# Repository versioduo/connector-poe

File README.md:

# ⚡ V2 Link + Power Over Ethernet Mode B 

## Board

## Schematic

[PDF](connector-poe.pdf)

## Bill Of Materials

[Interactive BOM](https://htmlpreview.github.io/?https://github.com/versioduo/connector-poe/main/connector-poe-bom.html)

# Copying
Anyone can use this public domain work without having to seek authorisation, no one can ever own it.

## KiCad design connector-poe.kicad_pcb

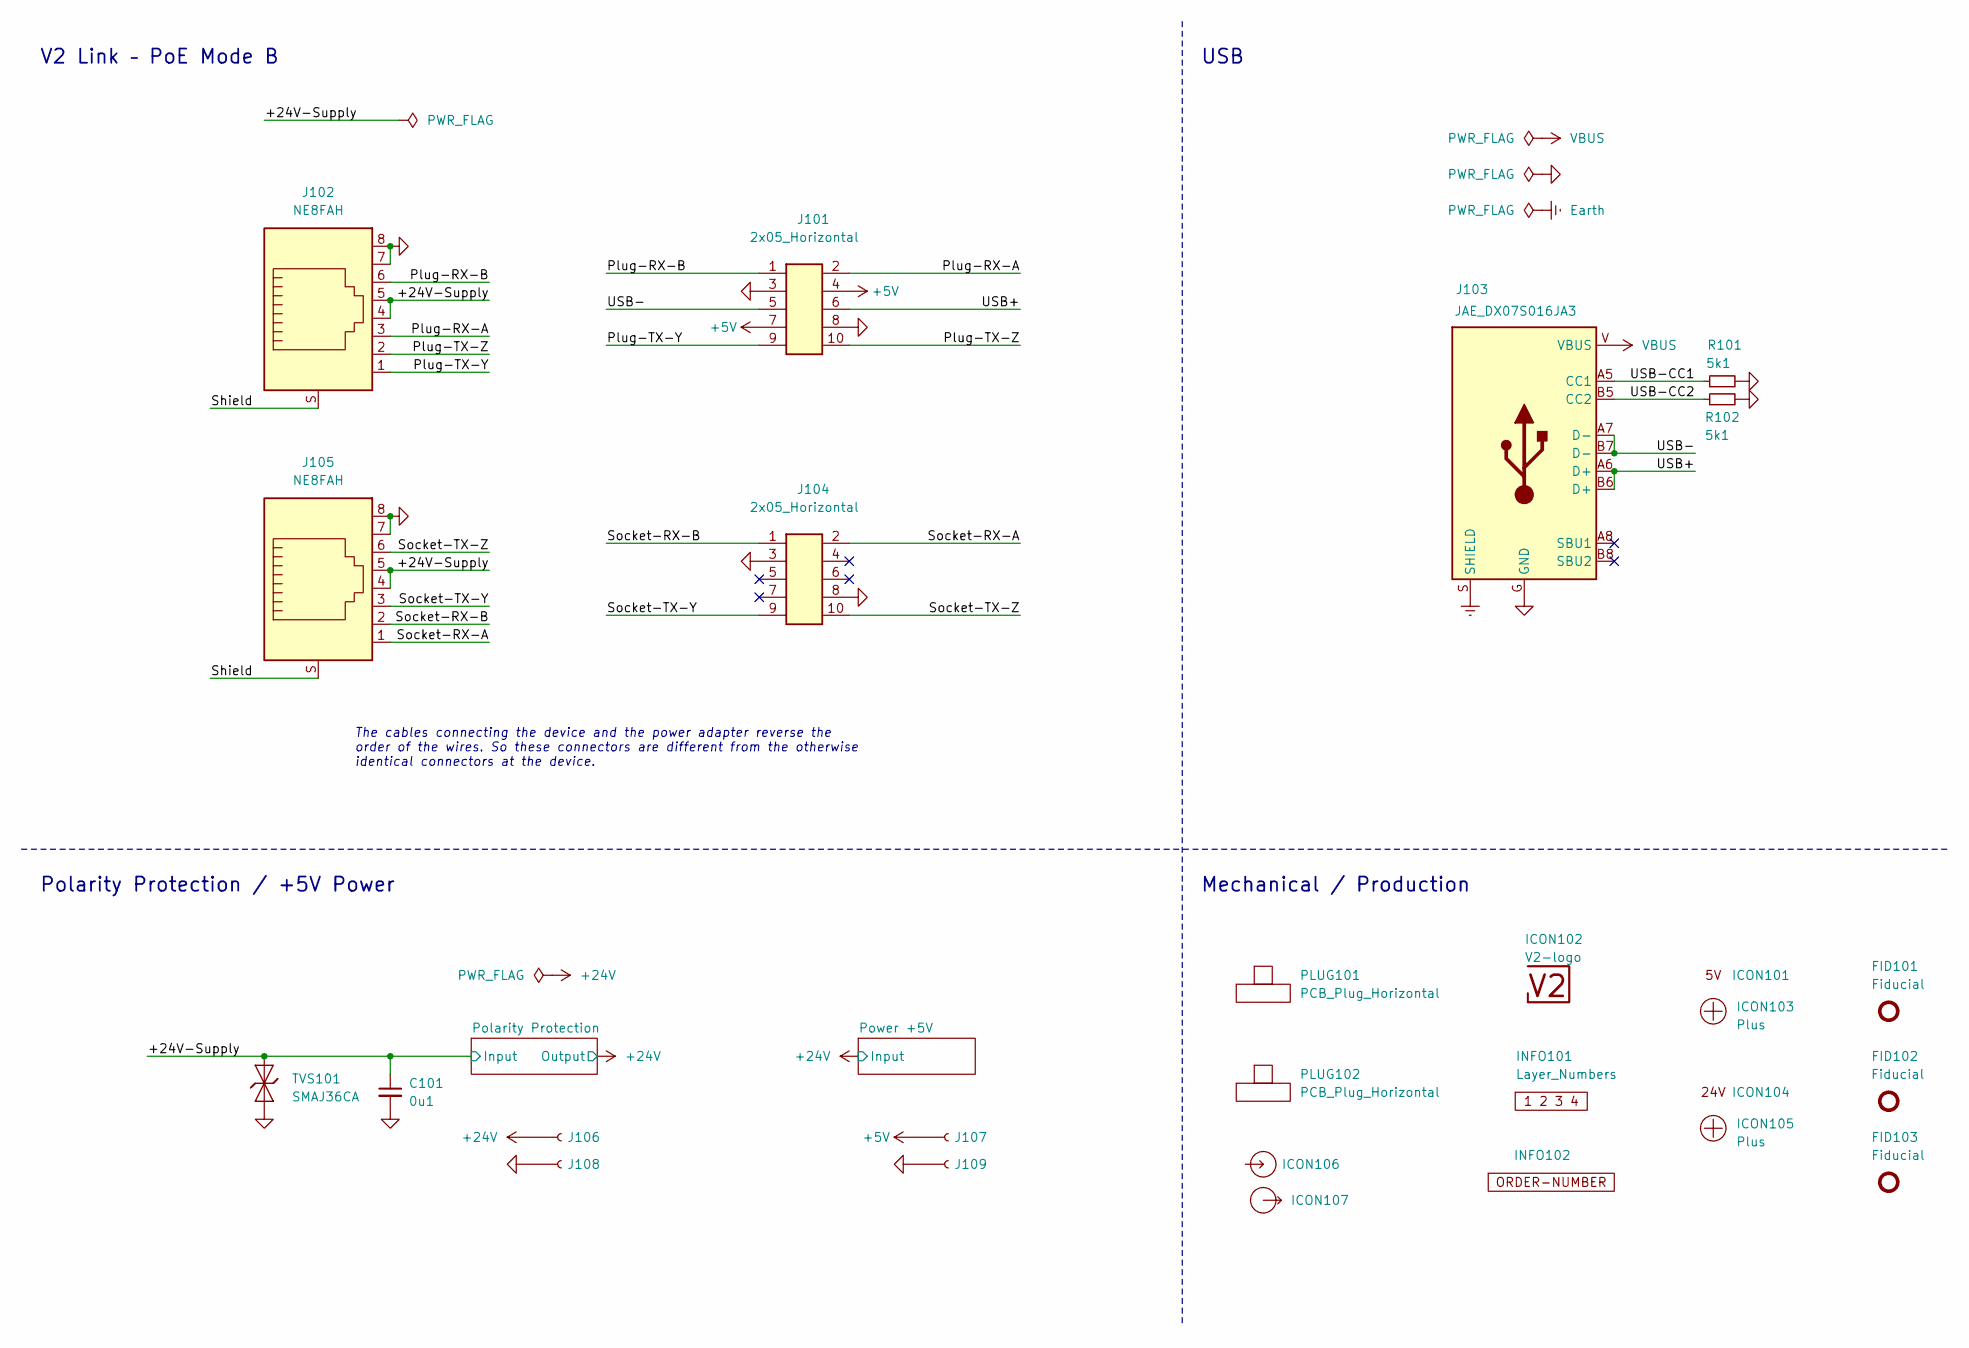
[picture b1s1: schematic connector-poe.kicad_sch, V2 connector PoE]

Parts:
C101: 0u1; C_0603_1608Metric
FID101, FID102, FID103: Fiducial; Fiducial_0.5mm_Mask1mm_Paste
ICON101: 5V
ICON102: V2-logo; Logo_Tiny
ICON103, ICON105: Plus; Plus_Small
ICON104: 24V
ICON106: Arrow_In
ICON107: Arrow_Out
INFO101: Layer_Numbers
INFO102: ORDER-NUMBER; Order_Number
J101, J104: 2x05_Horizontal; PinHeader_2x05_P1.27mm_Horizontal
J102, J105: NE8FAH
J103: JAE_DX07S016JA3
J106, J107, J108, J109: WAGO-2065; 2065-100
PLUG101, PLUG102: PCB_Plug_Horizontal
R101, R102: 5k1; R_0603_1608Metric
TVS101: SMAJ36CA; D_SMA

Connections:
+5V: J101.4, J101.7, J107.1; also elsewhere on the board
+24V: J106.1; also elsewhere on the board
/+24V-Supply: C101.1, J102.4, J102.5, J105.4, J105.5, TVS101.2 (A); also elsewhere on the board
/Plug-RX-A: J101.2, J102.3
/Plug-RX-B: J101.1, J102.6
/Plug-TX-Y: J101.9, J102.1
/Plug-TX-Z: J101.10, J102.2
/Shield: J102.S, J105.S
/Socket-RX-A: J104.2, J105.1
/Socket-RX-B: J104.1, J105.2
/Socket-TX-Y: J104.9, J105.3
/Socket-TX-Z: J104.10, J105.6
/USB+: J101.6, J103.A6 (D+), J103.B6 (D+)
/USB-: J101.5, J103.A7 (D-), J103.B7 (D-)
/USB-CC1: J103.A5 (CC1), R101.1
/USB-CC2: J103.B5 (CC2), R102.1
Earth: J103.S (SHIELD)
GND: C101.2, J101.3, J101.8, J102.7, J102.8, J103.G (GND), J104.3, J104.8, J105.7, J105.8, J108.1, J109.1, R101.2, R102.2, TVS101.1 (K); also elsewhere on the board
VBUS: J103.V (VBUS)

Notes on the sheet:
Polarity Protection / +5V Power
Mechanical / Production
The cables connecting the device and the power adapter reverse the order of the wires. So these connectors are different from the otherwise identical connectors at the device.
USB
V2 Link – PoE Mode B

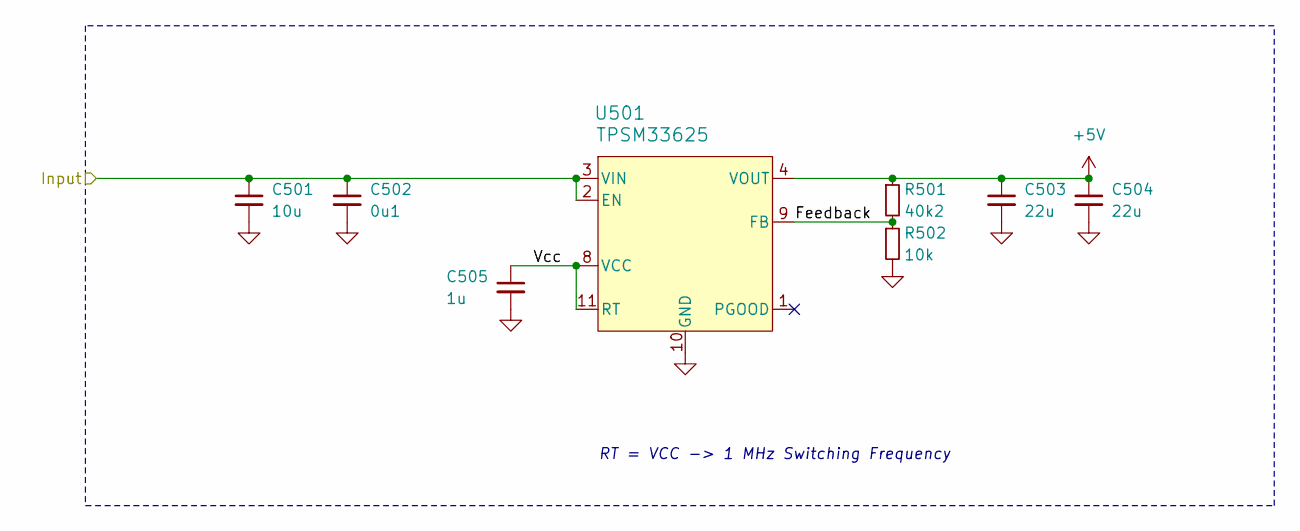
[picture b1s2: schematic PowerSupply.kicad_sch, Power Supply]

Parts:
C501: 10u; C_1210_3225Metric
C502: 0u1; C_0603_1608Metric
C503, C504: 22u; C_1210_3225Metric
C505: 1u; C_0603_1608Metric
R501: 40k2; R_0603_1608Metric
R502: 10k; R_0603_1608Metric
U501: TPSM33625

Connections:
+5V: C503.1, C504.1, R501.1, U501.4 (VOUT); also elsewhere on the board
+24V: C501.1, C502.1, U501.2 (EN), U501.3 (VIN); also elsewhere on the board
/Power +5V/Feedback: R501.2, R502.1, U501.9 (FB)
/Power +5V/Vcc: C505.1, U501.8 (VCC), U501.11 (RT)
GND: C501.2, C502.2, C503.2, C504.2, C505.2, R502.2, U501.10 (GND); also elsewhere on the board

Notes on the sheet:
RT = VCC -> 1 MHz Switching Frequency

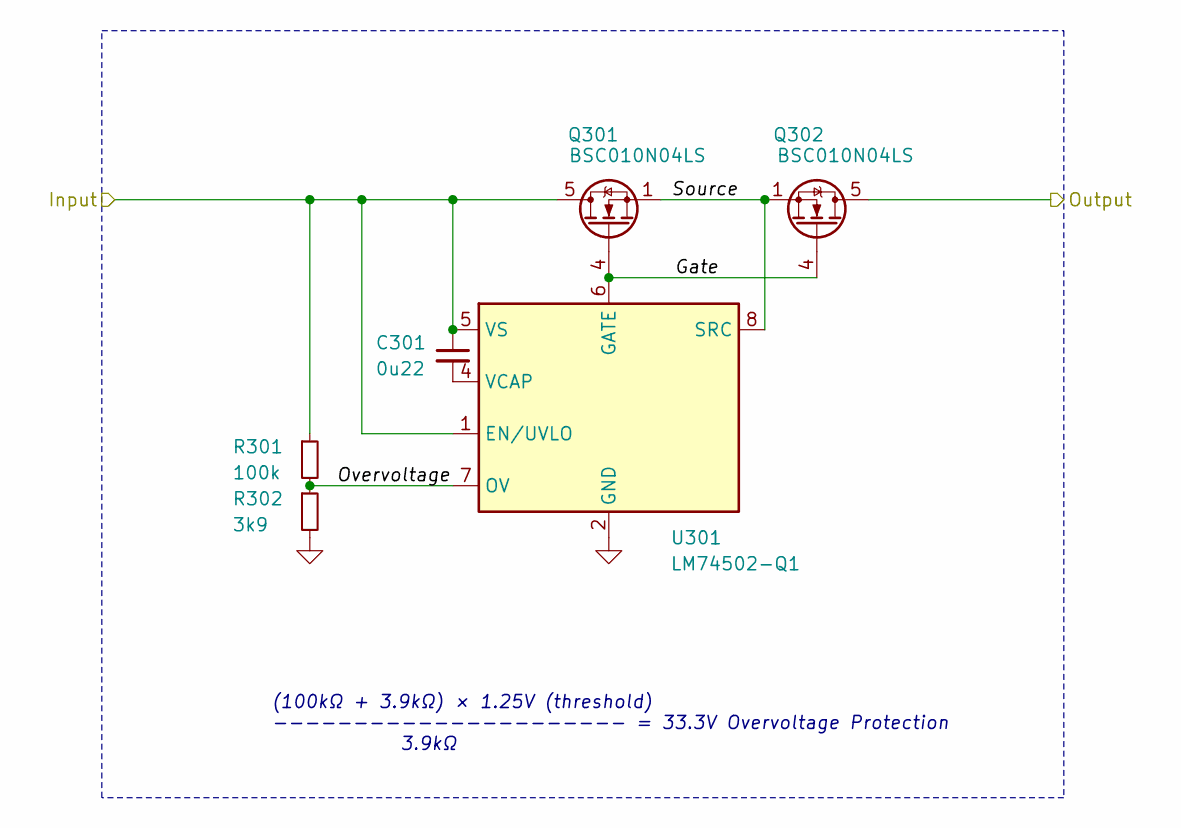
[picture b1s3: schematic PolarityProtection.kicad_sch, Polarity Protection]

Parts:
C301: 0u22; C_0603_1608Metric
Q301, Q302: BSC010N04LS; TDSON-8-FL
R301: 100k; R_0603_1608Metric
R302: 3k9; R_0603_1608Metric
U301: LM74502-Q1; SOT-23-8

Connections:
+24V: Q302.5 (D); also elsewhere on the board
/+24V-Supply: C301.1, Q301.5 (D), R301.1, U301.1 (EN/UVLO), U301.5 (VS); also elsewhere on the board
/Polarity Protection/Gate: Q301.4 (G), Q302.4 (G), U301.6 (GATE)
/Polarity Protection/Overvoltage: R301.2, R302.1, U301.7 (OV)
/Polarity Protection/Source: Q301.1 (S), Q302.1 (S), U301.8 (SRC)
GND: R302.2, U301.2 (GND); also elsewhere on the board
unnamed: C301.2, U301.4 (VCAP)

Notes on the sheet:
(100kΩ + 3.9kΩ) × 1.25V (threshold) ---------------------- = 33.3V Overvoltage Protection 3.9kΩ

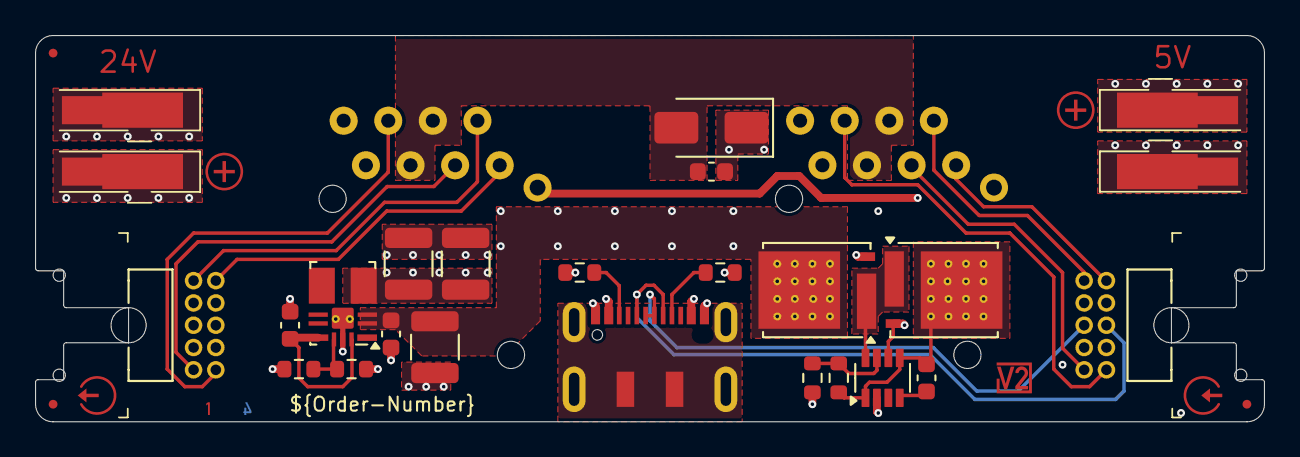
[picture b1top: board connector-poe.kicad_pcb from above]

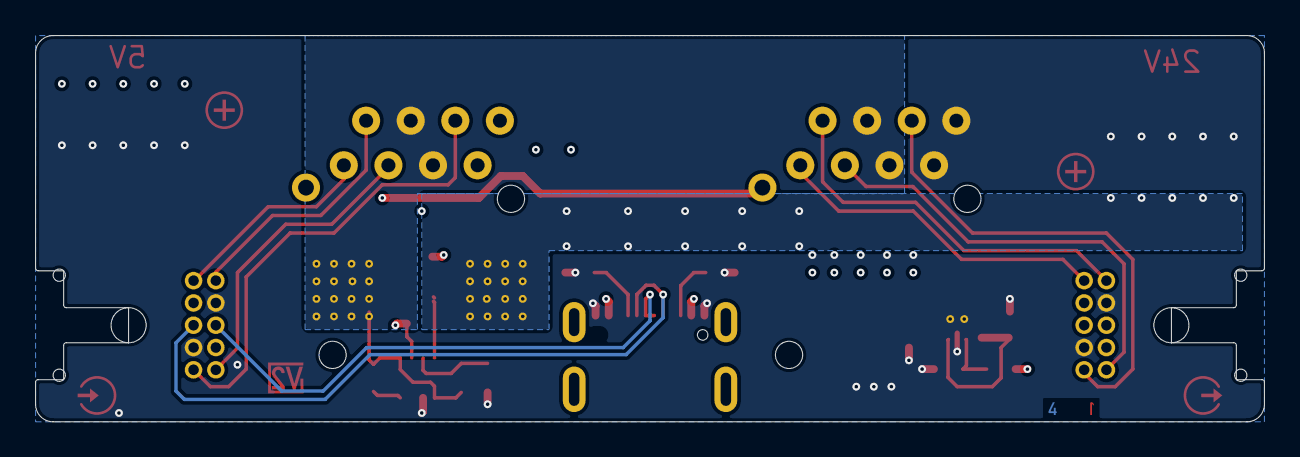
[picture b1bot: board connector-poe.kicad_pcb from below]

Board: 4 copper layers, 70.0 x 22.0 mm, 41 parts (2 on the bottom side), 23 nets.

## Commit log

2023-08-08 Import
2024-03-28 Update to Kicad 8
2024-03-28 Update DCDC
2024-06-20 Update icons
2024-06-20 Replace icons
2024-07-04 Rename to connector-poe
2025-09-17 Refresh
2025-10-25 Back-to-back Mosfet
2025-10-30 Resize to 70 mm
2025-10-30 GND label
